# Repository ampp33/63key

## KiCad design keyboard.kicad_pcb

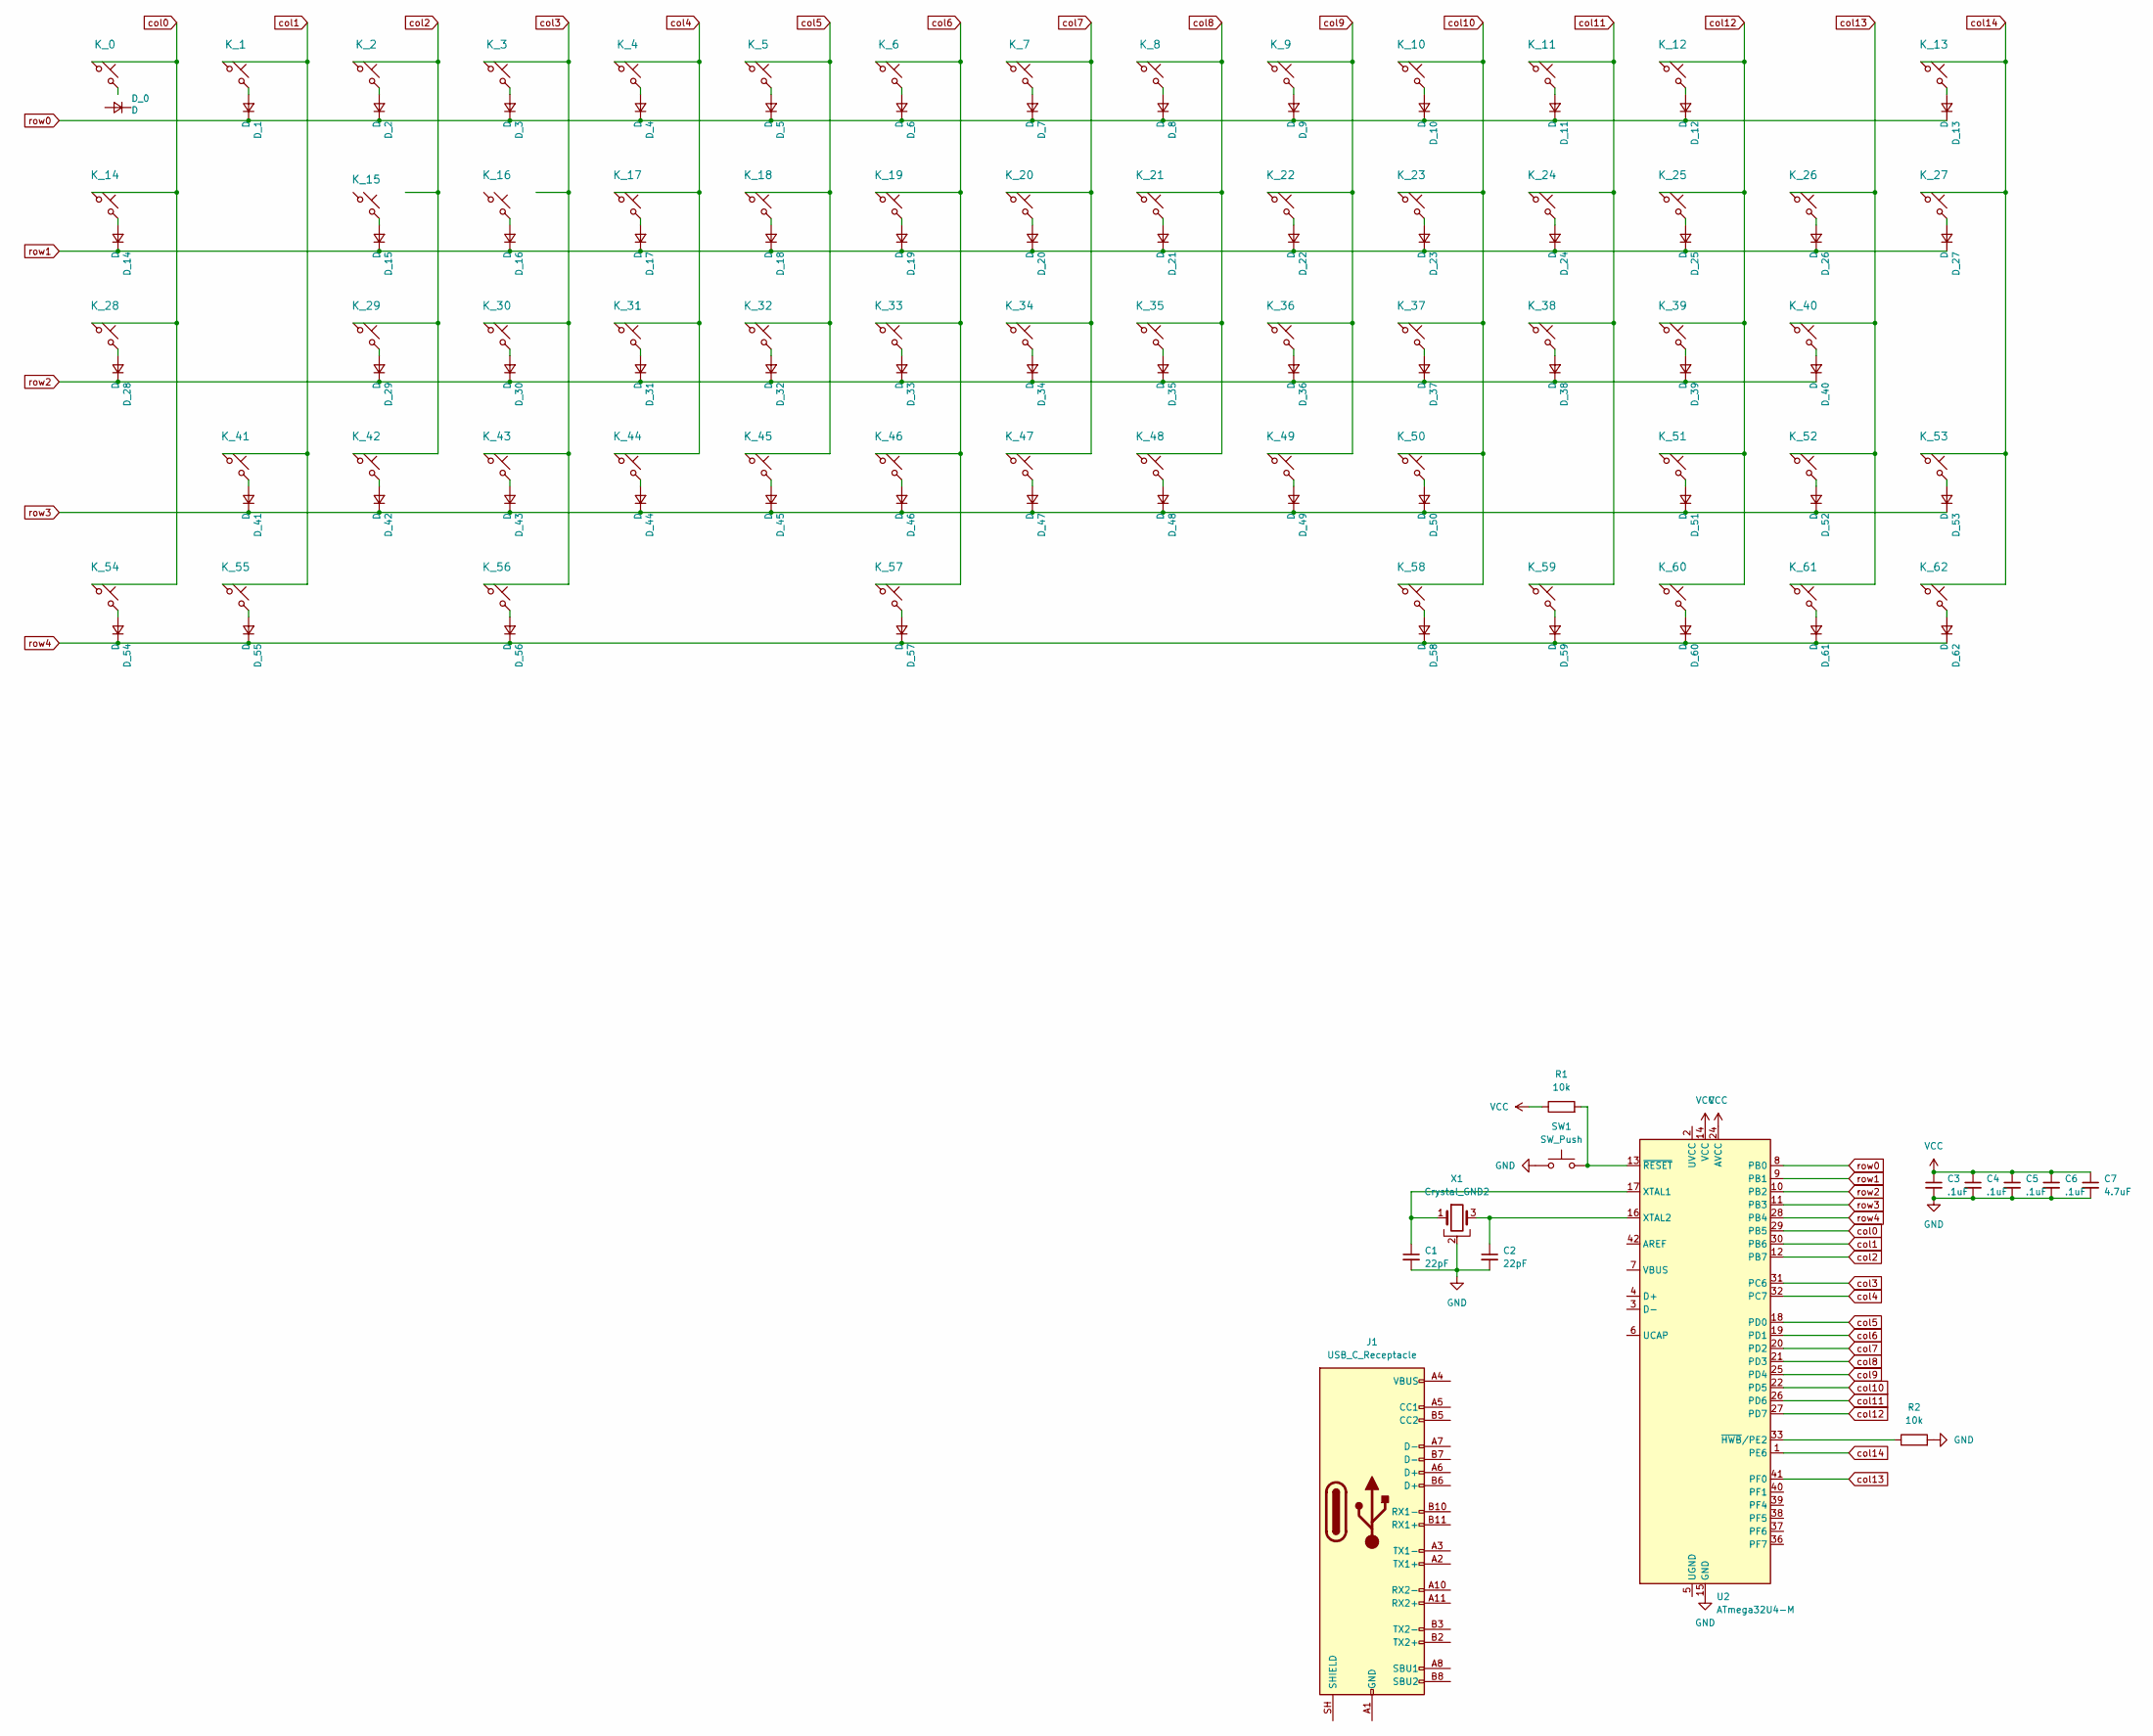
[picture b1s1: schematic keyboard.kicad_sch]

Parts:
C1, C2: 22pF; Capacitor_0402
C3, C4, C5, C6: .1uF; Capacitor_0402
C7: 4.7uF; Capacitor_0402
D_0, D_1, D_2, D_3, D_4, D_5, D_6, D_7, D_8, D_9, D_10, D_11, D_12, D_13, D_14, D_15, D_16, D_17, D_18, D_19, D_20, D_21, D_22, D_23, D_24, D_25, D_26, D_27, D_28, D_29, D_30, D_31, D_32, D_33, D_34, D_35, D_36, D_37, D_38, D_39, D_40, D_41, D_42, D_43, D_44, D_45, D_46, D_47, D_48, D_49, D_50, D_51, D_52, D_53, D_54, D_55, D_56, D_57, D_58, D_59, D_60, D_61, D_62: D; Diode_SOD-123
J1: USB_C_Receptacle; USB_C_HRO_TYPE-C-31-M-12
K_0, K_1, K_2, K_3, K_4, K_5, K_6, K_7, K_8, K_9, K_10, K_11, K_12, K_16, K_17, K_18, K_19, K_20, K_21, K_22, K_23, K_24, K_25, K_26, K_29, K_30, K_31, K_32, K_33, K_34, K_35, K_36, K_37, K_38, K_39, K_42, K_43, K_44, K_45, K_46, K_47, K_48, K_49, K_50, K_52, K_53, K_58, K_59, K_60, K_61, K_62: KEYSW; MX-1U-NoLED
K_13: KEYSW; MX-2U-NoLED
K_14, K_27: KEYSW; MX-1.5U-NoLED
K_15: KEYSW; MX_Solder_1.00u
K_28, K_51: KEYSW; MX-1.75U-NoLED
K_40, K_41: KEYSW; MX-2.25U-NoLED
K_54, K_55, K_56: KEYSW; MX-1.25U-NoLED
K_57: KEYSW; MX-6.25U-NoLED
R1, R2: 10k; Resistor_0402
SW1: SW_Push; Button_TL3342
U2: ATmega32U4-M; QFN-44-1EP_7x7mm_P0.5mm_EP5.2x5.2mm
X1: Crystal_GND2

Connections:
unnamed: C1.1, U2.17 (XTAL1), X1.1
unnamed: C2.1, U2.16 (XTAL2), X1.3
unnamed: D_1.2 (A), K_1.2
unnamed: D_2.2 (A), K_2.2
unnamed: D_3.2 (A), K_3.2
unnamed: D_4.2 (A), K_4.2
unnamed: D_5.2 (A), K_5.2
unnamed: D_6.2 (A), K_6.2
unnamed: D_7.2 (A), K_7.2
unnamed: D_8.2 (A), K_8.2
unnamed: D_9.2 (A), K_9.2
unnamed: D_10.2 (A), K_10.2
unnamed: D_11.2 (A), K_11.2
unnamed: D_12.2 (A), K_12.2
unnamed: D_13.2 (A), K_13.2
unnamed: D_14.2 (A), K_14.2
unnamed: D_15.2 (A), K_15.2 (2_2)
unnamed: D_16.2 (A), K_16.2 (2_2)
unnamed: D_17.2 (A), K_17.2
unnamed: D_18.2 (A), K_18.2
unnamed: D_19.2 (A), K_19.2
unnamed: D_20.2 (A), K_20.2
unnamed: D_21.2 (A), K_21.2
unnamed: D_22.2 (A), K_22.2
unnamed: D_23.2 (A), K_23.2
unnamed: D_24.2 (A), K_24.2
unnamed: D_25.2 (A), K_25.2
unnamed: D_26.2 (A), K_26.2
unnamed: D_27.2 (A), K_27.2
unnamed: D_28.2 (A), K_28.2
unnamed: D_29.2 (A), K_29.2
unnamed: D_30.2 (A), K_30.2
unnamed: D_31.2 (A), K_31.2
unnamed: D_32.2 (A), K_32.2
unnamed: D_33.2 (A), K_33.2
unnamed: D_34.2 (A), K_34.2
unnamed: D_35.2 (A), K_35.2
unnamed: D_36.2 (A), K_36.2
unnamed: D_37.2 (A), K_37.2
unnamed: D_38.2 (A), K_38.2
unnamed: D_39.2 (A), K_39.2
unnamed: D_40.2 (A), K_40.2
unnamed: D_41.2 (A), K_41.2
unnamed: D_42.2 (A), K_42.2
unnamed: D_43.2 (A), K_43.2
unnamed: D_44.2 (A), K_44.2
unnamed: D_45.2 (A), K_45.2
unnamed: D_46.2 (A), K_46.2
unnamed: D_47.2 (A), K_47.2
unnamed: D_48.2 (A), K_48.2
unnamed: D_49.2 (A), K_49.2
unnamed: D_50.2 (A), K_50.2
unnamed: D_51.2 (A), K_51.2
unnamed: D_52.2 (A), K_52.2
unnamed: D_53.2 (A), K_53.2
unnamed: D_54.2 (A), K_54.2
unnamed: D_55.2 (A), K_55.2
unnamed: D_56.2 (A), K_56.2
unnamed: D_57.2 (A), K_57.2
unnamed: D_58.2 (A), K_58.2
unnamed: D_59.2 (A), K_59.2
unnamed: D_60.2 (A), K_60.2
unnamed: D_61.2 (A), K_61.2
unnamed: D_62.2 (A), K_62.2
unnamed: J1.A1 (GND), J1.A12 (GND), J1.B1 (GND), J1.B12 (GND)
unnamed: J1.A4 (VBUS), J1.A9 (VBUS), J1.B4 (VBUS), J1.B9 (VBUS)
unnamed: R1.2, SW1.2, U2.13 (~RESET)
unnamed: C1.2, C2.2, C3.2, C4.2, C5.2, C6.2, C7.2, R2.2, SW1.1, U2.15 (GND), U2.23 (GND), U2.35 (GND), U2.43 (GND), U2.45 (GND), X1.2
col0: K_0.1 (1_1), K_14.1, K_28.1, K_54.1, U2.29 (PB5)
col1: K_1.1, K_41.1, K_55.1, U2.30 (PB6)
col2: K_2.1, K_29.1, K_42.1, U2.12 (PB7)
col3: K_3.1, K_30.1, K_43.1, K_56.1, U2.31 (PC6)
col4: K_4.1, K_17.1, K_31.1, K_44.1, U2.32 (PC7)
col5: K_5.1, K_18.1, K_32.1, K_45.1, U2.18 (PD0)
col6: K_6.1, K_19.1, K_33.1, K_46.1, K_57.1, U2.19 (PD1)
col7: K_7.1, K_20.1, K_34.1, K_47.1, U2.20 (PD2)
col8: K_8.1, K_21.1, K_35.1, K_48.1, U2.21 (PD3)
col9: K_9.1, K_22.1, K_36.1, K_49.1, U2.25 (PD4)
col10: K_10.1, K_23.1, K_37.1, K_50.1, K_58.1, U2.22 (PD5)
col11: K_11.1, K_24.1, K_38.1, K_59.1, U2.26 (PD6)
col12: K_12.1, K_25.1, K_39.1, K_51.1, K_60.1, U2.27 (PD7)
col13: K_26.1, K_40.1, K_52.1, K_61.1, R2.1, U2.33 (~HWB/PE2), U2.41 (PF0)
col14: K_13.1, K_27.1, K_53.1, K_62.1, U2.1 (PE6)
row0: D_1.1 (K), D_2.1 (K), D_3.1 (K), D_4.1 (K), D_5.1 (K), D_6.1 (K), D_7.1 (K), D_8.1 (K), D_9.1 (K), D_10.1 (K), D_11.1 (K), D_12.1 (K), D_13.1 (K), U2.8 (PB0)
row1: D_14.1 (K), D_15.1 (K), D_16.1 (K), D_17.1 (K), D_18.1 (K), D_19.1 (K), D_20.1 (K), D_21.1 (K), D_22.1 (K), D_23.1 (K), D_24.1 (K), D_25.1 (K), D_26.1 (K), D_27.1 (K), U2.9 (PB1)
row2: D_28.1 (K), D_29.1 (K), D_30.1 (K), D_31.1 (K), D_32.1 (K), D_33.1 (K), D_34.1 (K), D_35.1 (K), D_36.1 (K), D_37.1 (K), D_38.1 (K), D_39.1 (K), D_40.1 (K), U2.10 (PB2)
row3: D_41.1 (K), D_42.1 (K), D_43.1 (K), D_44.1 (K), D_45.1 (K), D_46.1 (K), D_47.1 (K), D_48.1 (K), D_49.1 (K), D_50.1 (K), D_51.1 (K), D_52.1 (K), D_53.1 (K), U2.11 (PB3)
row4: D_54.1 (K), D_55.1 (K), D_56.1 (K), D_57.1 (K), D_58.1 (K), D_59.1 (K), D_60.1 (K), D_61.1 (K), D_62.1 (K), U2.28 (PB4)

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
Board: 2 copper layers, 127 parts (63 on the bottom side), 85 nets, no tracks yet.
